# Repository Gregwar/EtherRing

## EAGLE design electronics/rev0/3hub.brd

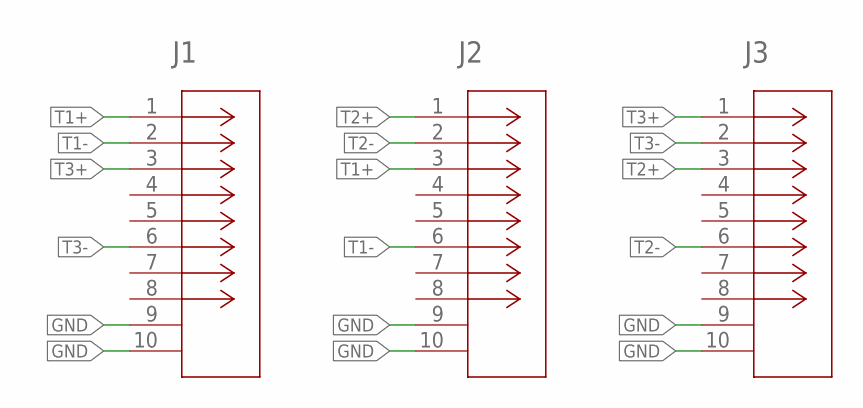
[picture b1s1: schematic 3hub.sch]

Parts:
J1, J2, J3: 1-406541-1; CONN8_406541_TEC

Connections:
GND: J1.9, J1.10, J2.9, J2.10, J3.9, J3.10
T1+: J1.1, J2.3
T1-: J1.2, J2.6
T2+: J2.1, J3.3
T2-: J2.2, J3.6
T3+: J1.3, J3.1
T3-: J1.6, J3.2

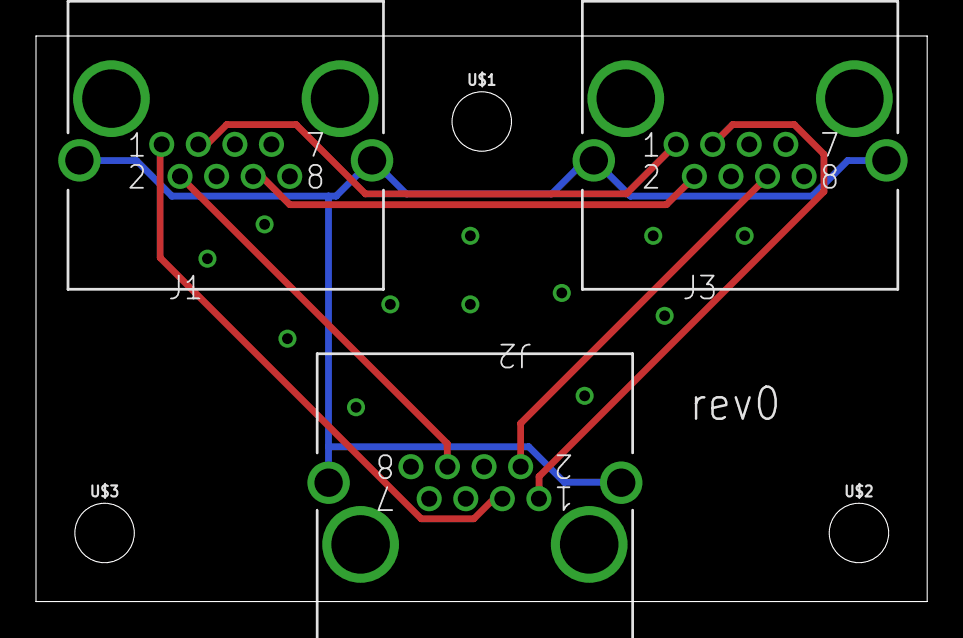
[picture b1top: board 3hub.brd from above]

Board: 2 copper layers, 49.5 x 31.4 mm, 6 parts (0 on the bottom side), 7 nets.

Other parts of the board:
U$1, U$2, U$3: STAND-OFF

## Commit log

2021-11-22 Board
2021-11-22 3hub
2021-12-02 Fixing connectors orientation...

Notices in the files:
parts and their libraries:
SparkFun-Hardware: Licensing: Creative Commons ShareAlike 4.0 International - https://creativecommons.org/licenses/by-sa/4.0
COPYRIGHT: Copyright (C) 2021 Ultra Librarian. All rights reserved.
